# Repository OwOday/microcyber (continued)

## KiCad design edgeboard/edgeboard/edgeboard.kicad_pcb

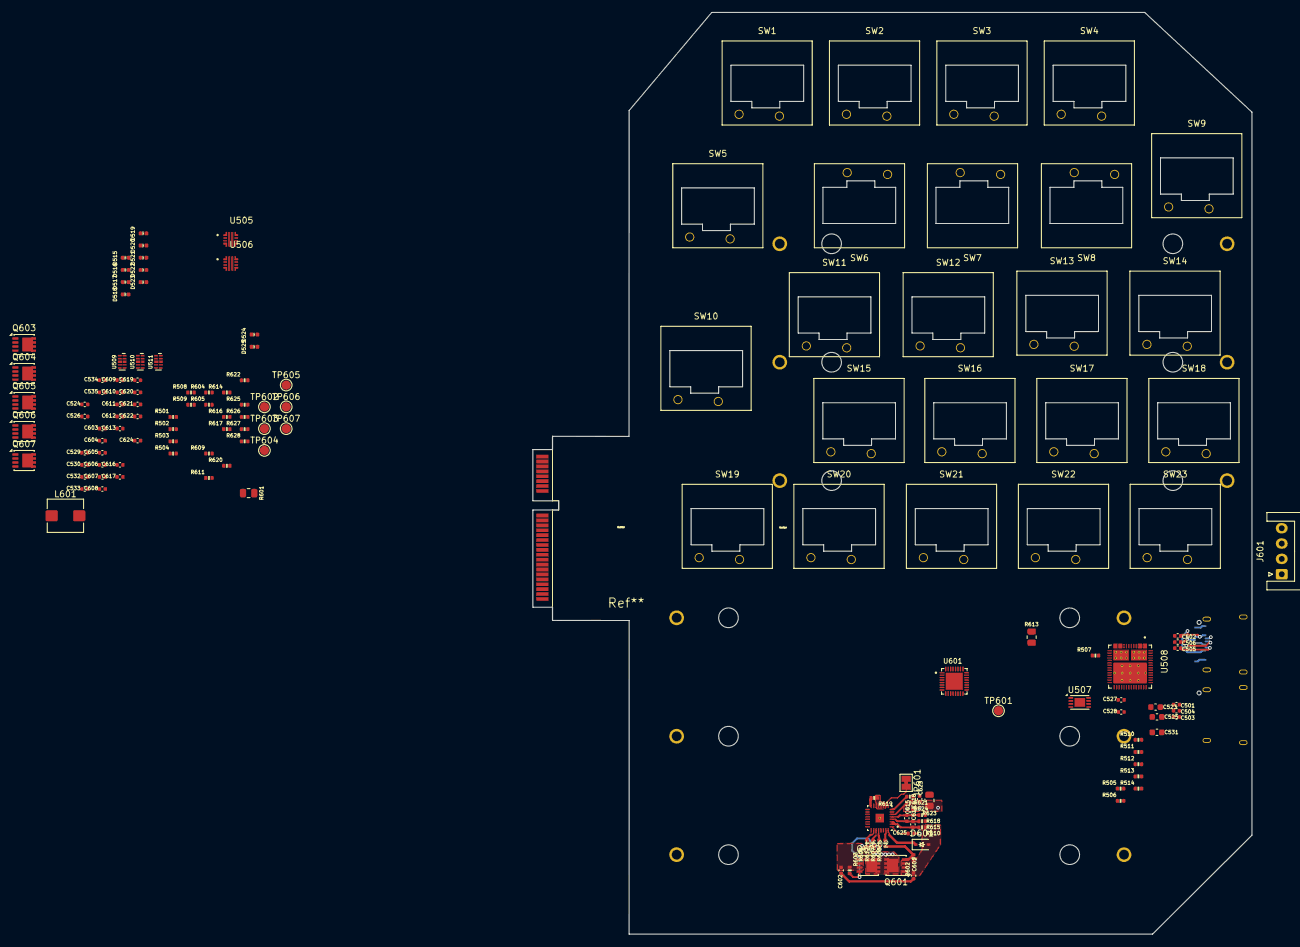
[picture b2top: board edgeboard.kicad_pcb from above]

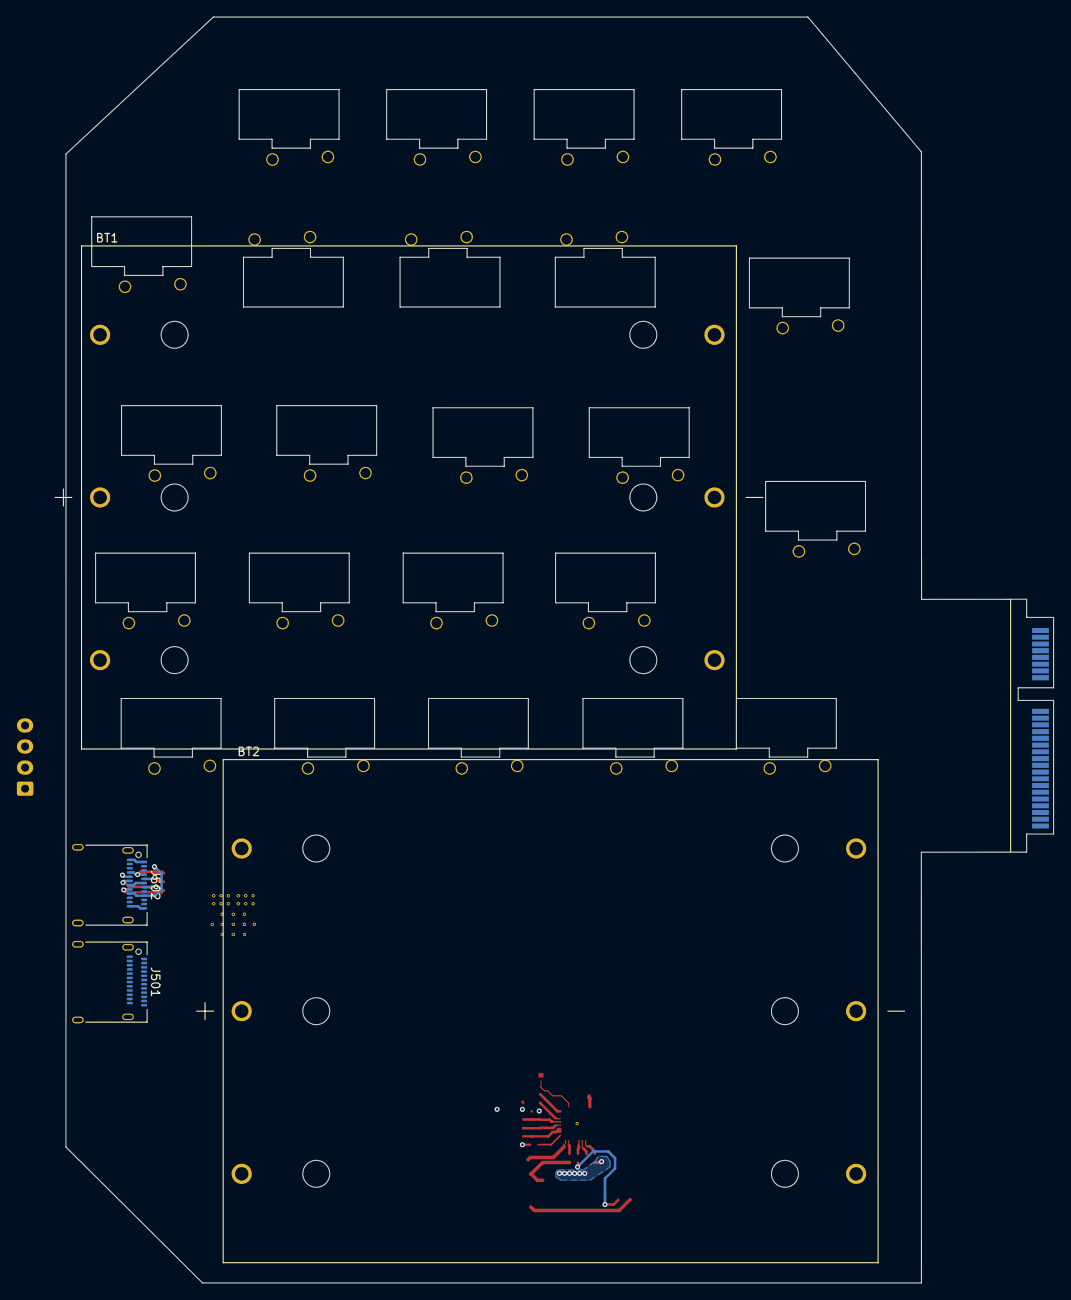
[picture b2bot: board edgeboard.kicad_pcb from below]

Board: 2 copper layers, 117.2 x 150.2 mm, 152 parts (4 on the bottom side), 101 nets.

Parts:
BT1, BT2: BK-18650-PC6; BAT_BK-18650-PC6
C501, C502, C524, C526, C527, C532, C533: 100nF/50V; C_0402_1005Metric
C503, C504, C505, C506: 47pF; C_0402_1005Metric
C523: 22uF/10V; C_0603_1608Metric
C525, C531: 10uF/10V; C_0603_1608Metric
C528: 4.7uF/10V; C_0402_1005Metric
C529, C530, C534, C535: 47pF/50V; C_0402_1005Metric
C601, C602, C613, C614, C615, C618, C623: 0.1u; C_0402_1005Metric
C603: 3x10uF MLCC; C_0402_1005Metric
C604, C605: 47n; C_0402_1005Metric
C606, C607, C608, C609: 10uF MLCC; C_0402_1005Metric
C610, C611: 33n; C_0402_1005Metric
C612: 0.47u; C_0402_1005Metric
C616: 33p; C_0402_1005Metric
C617: 1800p; C_0402_1005Metric
C619: 1u; C_0402_1005Metric
C620, C625: 2.2u; C_0402_1005Metric
C621: 15p; C_0402_1005Metric
C622: 680p; C_0402_1005Metric
C624: 100p; C_0402_1005Metric
D515, D516, D517, D518, D519, D520, D521, D522, D523, D524, D525: ESD9B3.3ST5GOSCT-ND; D_0402_1005Metric
D601: BAT54HT1; D_SOD-323
J501, J502: USB_C_Receptacle; USB_C_Receptacle_Amphenol_12401610E4-2A
J601: JST XH 4 pin; JST_XH_S4B-XH-A_1x04_P2.50mm_Horizontal
JP601: Jumper_2_Bridged; SolderJumper-2_P1.3mm_Bridged_Pad1.0x1.5mm
L601: 2.2uH 4.5A+; L_Bourns_SRP5030T
Q601, Q602, Q603, Q604, Q605, Q606: CSD17551Q3A; Vishay_PowerPAK_1212-8_Single
Q607: CSD25402Q3A; Vishay_PowerPAK_1212-8_Single
R501, R502, R503, R504, R508, R509, R510, R511, R512: 100K/1%; R_0402_1005Metric
R505, R506: 10K/1%; R_0402_1005Metric
R507: 100K; R_0402_1005Metric
R513, R612, R619: 10K; R_0402_1005Metric
R514: 19.1K/1%; R_0402_1005Metric
R601, R613: 10m; R_0805_2012Metric
R602, R603: 10M; R_0402_1005Metric
R604, R605: 4.99; R_0402_1005Metric
R606, R607: 5.1k; R_0402_1005Metric
R608, R610, R615, R618, R621, R624: 100; R_0402_1005Metric
R609: 1; R_0402_1005Metric
R611, R614, R617: 10; R_0402_1005Metric
R616: 40.2k; R_0402_1005Metric
R620: 10k; R_0402_1005Metric
R622, R625, R626, R628: TBD; R_0402_1005Metric
R623: 0.001; R_0805_2012Metric
R627: 137K; R_0402_1005Metric
Ref**: Val**; mpcie-full-card
SW1, SW2, SW3, SW4: SW_Push; SW_Kailh_Choc_Mini_1.25u_90deg
SW5: SW_Push; SW_Kailh_Choc_Mini_1.50u
SW6, SW7, SW8, SW11, SW12, SW13, SW14, SW15, SW16, SW17, SW18, SW19, SW20, SW21, SW22, SW23: SW_Push; SW_Kailh_Choc_Mini_1.00u
SW9: SW_Push; SW_Kailh_Choc_Mini_1.50u_90deg
SW10: SW_Push; SW_Kailh_Choc_Mini_ISOEnter_180deg
TP601: VBAT; TestPoint_Pad_D1.5mm
TP602: VCHARGE; TestPoint_Pad_D1.5mm
TP603: VSYSTEM; TestPoint_Pad_D1.5mm
TP604: PSYS; TestPoint_Pad_D1.5mm
TP605: PROCHOT; TestPoint_Pad_D1.5mm
TP606: IBAT; TestPoint_Pad_D1.5mm
TP607: CHRG_OK; TestPoint_Pad_D1.5mm
U505, U506: LM73100RPWR; IC_LM73100RPWR
U507: AT25DN512C-MAHF-T; DFN-8-1EP_3x2mm_P0.5mm_EP1.75x1.45mm
U508: TPS65988DHRSHR; IC_TPS65987DDHRSHR
U509, U510, U511: ULC0524P; Diodes_UDFN-10_1.0x2.5mm_P0.5mm
U601: BQ25710RSNT; QFN40P400X400X80-33N
U602: BQ40Z50RSMR-R2; QFN40P400X400X100-33N

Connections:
+3V3: C531.2, U508.5 (VIN_3V3)
+3V3_TPS: C525.2, C527.2, R505.2, R506.2, R512.1, U507.8 (VCC), U508.9 (LDO_3V3)
+5V: C528.2, U508.25 (PP1_CABLE), U508.46 (PP2_CABLE)
+12v: Ref**.38, Ref**.39, Ref**.40, Ref**.41, Ref**.42, Ref**.43, Ref**.44, Ref**.45, Ref**.46, Ref**.47, Ref**.48, Ref**.49, Ref**.50, Ref**.51, Ref**.52
/-BATT: C623.1, J601.4, R621.1, R623.1
/DISP1_HPD: R510.1, U508.30 (GPIO3(HPD1))
/DISP2_HPD: R511.1, U508.31 (GPIO4(HPD2))
/EXT_VBUS_SOURCE1: R501.2, U506.1 (EN/UVLO), U508.48 (GPIO16(PP_EXT1))
/EXT_VBUS_SOURCE2: R502.2, U505.1 (EN/UVLO), U508.49 (GPIO17(PP_EXT2))
/GPIO_1: D517.2 (A2), U511.1, U511.10 (NC)
/GPIO_2: D516.2 (A2), U511.4, U511.7 (NC)
/GPIO_3: D515.2 (A2), U511.2, U511.9 (NC)
/GPIO_4: D518.2 (A2), U511.5, U511.6 (NC)
/GPIO_5: D519.2 (A2), U510.1, U510.10 (NC)
/GPIO_6: D520.2 (A2), U510.4, U510.7 (NC)
/GPIO_7: D521.2 (A2), U510.2, U510.9 (NC)
/GPIO_8: D522.2 (A2), U510.5, U510.6 (NC)
/PACK+: C601.1, D601.2 (A), J601.1, Q601.1 (S), Q601.2 (S), Q601.3 (S), R602.1, R610.1
/SMB_ALERT: D525.2 (A2), U509.4, U509.7 (NC)
/SMB_CLK: D524.2 (A2), U509.2, U509.9 (NC), U601.13 (SCL), U602.19 (SMBC)
/SMB_DATA: D523.2 (A2), U509.1, U509.10 (NC), U601.12 (SDA), U602.18 (SMBD)
/USBC1_CC1: C504.1, J501.A5 (CC1), U508.24 (C1_CC1)
/USBC1_CC2: C503.1, J501.B5 (CC2), U508.26 (C1_CC2)
/USBC1_SBU1: C524.2, C529.1, J501.A8 (SBU1), R504.2
/USBC1_SBU2: C526.2, C530.1, J501.B8 (SBU2), R503.2
/USBC1_USB2_D+: J501.A6 (D+), J501.B6 (D+)
/USBC1_USB2_D-: J501.A7 (D-), J501.B7 (D-)
/USBC1_VBUS: C501.1, J501.A4 (VBUS), J501.A9 (VBUS), J501.B4 (VBUS), J501.B9 (VBUS), U506.6 (OUT), U508.13 (VBUS1)
/USBC2_CC1: C506.1, J502.A5 (CC1), U508.45 (C2_CC1)
/USBC2_CC2: C505.1, J502.B5 (CC2), U508.47 (C2_CC2)
/USBC2_SBU1: C532.2, C534.1, J502.A8 (SBU1), R509.2
/USBC2_SBU2: C533.2, C535.1, J502.B8 (SBU2), R508.2
/USBC2_USB2_D+: J502.A6 (D+), J502.B6 (D+)
/USBC2_USB2_D-: J502.A7 (D-), J502.B7 (D-)
/USBC2_VBUS: C502.1, J502.A4 (VBUS), J502.A9 (VBUS), J502.B4 (VBUS), J502.B9 (VBUS), U505.6 (OUT), U508.3 (VBUS2)
/VBAT: C602.2, C613.2, Q602.1 (S), Q602.2 (S), Q602.3 (S), R603.1, R612.1, R613.1, R614.1, TP601.1 (1_1)
/VBATSNS: C613.1, Q607.1 (D), Q607.2 (D), Q607.3 (D), R611.1, R613.2
/VBUS_5VIN: U505.5 (IN), U506.5 (IN)
/VCHARGE: C603.1, R601.1, R604.1, R609.1, TP602.1 (1_1), U508.1 (PP_HV2), U508.11 (PP_HV1)
/VSYSTEM: C606.1, C607.1, C608.1, C609.1, Q604.5 (D), Q607.5 (S), TP603.1 (1_1), U601.22 (VSYS)
GND: C501.2, C502.2, C503.2, C504.2, C505.2, C506.2, C523.1, C525.1, C527.1, C528.1, C529.2, C530.2, C531.1, C534.2, C535.2, C603.2, C606.2, C607.2, C608.2, C609.2, C610.2, C611.2, C612.2, C616.2, C617.2, C618.1, C619.2, C620.2, C621.2, C622.2, C623.2, C624.2, C625.2, D515.1 (A1), D516.1 (A1), D517.1 (A1), D518.1 (A1), D519.1 (A1), D520.1 (A1), D521.1 (A1), D522.1 (A1), D523.1 (A1), D524.1 (A1), D525.1 (A1), J501.A1 (GND), J501.A12 (GND), J501.B1 (GND), J501.B12 (GND), J502.A1 (GND), J502.A12 (GND), J502.B1 (GND), J502.B12 (GND), JP601.1 (A), Q605.1 (S), Q605.2 (S), Q605.3 (S), Q606.1 (S), Q606.2 (S), Q606.3 (S), R501.1, R502.1, R507.1, R510.2, R511.2, R513.1, R514.2, R619.1, R623.2, R624.1, R625.2, R627.2, R628.2, Ref**.17, Ref**.18, Ref**.19, Ref**.20, Ref**.21, Ref**.22, Ref**.23, Ref**.24, Ref**.25, Ref**.26, Ref**.27, Ref**.29, U505.2 (OVLO), U505.4 (PGTH), U505.8 (GND), U505.9 (IMON), U506.2 (OVLO), U506.4 (PGTH), U506.8 (GND), U506.9 (IMON), U507.4 (GND), U507.9 (GND), U508.10 (ADCIN2), U508.20 (GND), U508.51 (GND__1), U508.59 (THERMALPAD(PPAD)), U508.59_1 (THERMALPAD(PPAD)), U508.59_2 (THERMALPAD(PPAD)), U508.59_3 (THERMALPAD(PPAD)), U508.59_4 (THERMALPAD(PPAD)), U508.59_5 (THERMALPAD(PPAD)), U508.59_6 (THERMALPAD(PPAD)), U508.59_7 (THERMALPAD(PPAD)), U508.59_8 (THERMALPAD(PPAD)), U508.59_9 (THERMALPAD(PPAD)), U508.59_10 (THERMALPAD(PPAD)), U508.59_11 (THERMALPAD(PPAD)), U509.3 (VSS), U509.8 (VSS), U510.3 (VSS), U510.8 (VSS), U511.3 (VSS), U511.8 (VSS), U601.5 (OTG/VAP), U601.14 (CMPIN), U601.27 (PGND), U602.9 (VSS), U602.11 (TS2), U602.12 (TS3), U602.13 (TS4), U602.17 (~DISP), U602.23 (PTC), U602.24 (PTCEN), U602.33 (EXP), U602.33_1 (EXP__1)
unnamed: C601.2, C602.1
unnamed: C617.1, R616.2
unnamed: C622.1, R620.2
unnamed: D601.1 (K), U602.32 (BAT)
unnamed: J601.2, R615.1
unnamed: J601.3, R618.1
unnamed: JP601.2 (B), U602.10 (TS1)
unnamed: Q601.5 (D), Q602.5 (D), R608.1
unnamed: Q601.4 (G), R602.2, R606.1
unnamed: Q602.4 (G), R603.2, R607.1
unnamed: Q603.5 (D), R601.2, R605.1
unnamed: Q603.4 (G), U601.31 (HIDRV1)
unnamed: Q604.4 (G), U601.24 (HIDRV2)
unnamed: C604.1, L601.1, Q603.1 (S), Q603.2 (S), Q603.3 (S), Q605.5 (D), U601.32 (SW1)
unnamed: Q605.4 (G), U601.29 (LODRV1)
unnamed: C605.1, L601.2, Q604.1 (S), Q604.2 (S), Q604.3 (S), Q606.5 (D), U601.23 (SW2)
unnamed: Q606.4 (G), U601.26 (LODRV2)
unnamed: Q607.4 (G), U601.21 (~BATDRV)
unnamed: U507.2 (MISO), U508.36 (SPI_POCI)
unnamed: U507.5 (MOSI), U508.37 (SPI_PICO)
unnamed: U507.6 (SCK), U508.38 (SPI_CLK)
unnamed: U507.1 (~CS), U508.39 (~SPI_CS)
unnamed: R512.2, R514.1, U508.6 (ADCIN1)
unnamed: U508.8 (DRAIN1), U508.15 (DRAIN1__1), U508.19 (DRAIN1__2), U508.58 (DRAIN1__3), U508.58_1 (DRAIN1_PAD), U508.58_2 (DRAIN1_PAD), U508.58_3 (DRAIN1_PAD), U508.58_4 (DRAIN1_PAD), U508.58_5 (DRAIN1_PAD), U508.58_6 (DRAIN1_PAD)
unnamed: U508.7 (DRAIN2), U508.52 (DRAIN2__1), U508.56 (DRAIN2__2), U508.57 (DRAIN2__3), U508.57_1 (DRAIN2_PAD), U508.57_2 (DRAIN2_PAD), U508.57_3 (DRAIN2_PAD), U508.57_4 (DRAIN2_PAD), U508.57_5 (DRAIN2_PAD), U508.57_6 (DRAIN2_PAD)
unnamed: R507.2, U508.17 (GPIO1)
unnamed: R513.2, U508.44 (HRESET)
unnamed: R505.1, U508.27 (I2C1_SCL)
unnamed: R506.1, U508.28 (I2C1_SDA)
unnamed: C523.2, U508.35 (LDO_1V8)
unnamed: U509.5, U509.6 (NC)
unnamed: C611.1, R605.2, U601.2 (ACN)
unnamed: C610.1, R604.2, U601.3 (ACP)
unnamed: C604.2, U601.30 (BTST1)
unnamed: C605.2, U601.25 (BTST2)
unnamed: R622.2, R625.1, U601.18 (CELL_BATPRESZ)
unnamed: TP607.1 (1_1), U601.4 (CHRG_OK)
unnamed: C616.1, R616.1, U601.16 (COMP1)
unnamed: C621.1, R620.1, U601.17 (COMP2)
unnamed: C624.1, R627.1, U601.8 (IADPT)
unnamed: TP606.1 (1_1), U601.9 (IBAT)
unnamed: R626.2, R628.1, U601.6 (ILIM_HIZ)
unnamed: TP604.1 (1_1), U601.10 (PSYS)
unnamed: C620.1, R617.2, U601.28 (REGN)
unnamed: R614.2, U601.19 (SRN)
unnamed: R611.2, U601.20 (SRP)
unnamed: C612.1, R609.2, U601.1 (VBUS)
unnamed: C619.1, R617.1, R622.1, R626.1, U601.7 (VDDA)
unnamed: TP605.1 (1_1), U601.11 (~PROCHOT)
unnamed: R606.2, U602.31 (CHG)
unnamed: R607.2, U602.28 (DSG)
unnamed: R612.2, U602.27 (PACK)
unnamed: C625.1, U602.1 (PBI)
unnamed: R624.2, U602.6 (SRN)
unnamed: R621.2, U602.8 (SRP)
unnamed: C615.1, C618.2, R618.2, U602.5 (VC1)
unnamed: C614.1, C615.2, R615.2, U602.4 (VC2)
unnamed: C614.2, R610.2, U602.2 (VC4), U602.3 (VC3)
unnamed: R608.2, U602.26 (VCC)
unnamed: R619.2, U602.16 (~PRES/~SHUTDN)

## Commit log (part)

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2026-03-20 initial
2026-03-21 more work on custom usb-c power
2026-03-26 finished schematic draft and started placing components
2026-03-28 commit before removing duplicated glasgow
2026-03-29 is this a differential pair?
2026-03-29 differential pairs fixed?
2026-03-30 before board exclusion
2026-03-30 REV 0
2026-04-06 went back to the drawing board
2026-04-07 some power stuff (unfinished)
2026-04-07 power finished started diff pairs
2026-04-07 rpi edgeboard
2026-04-07 fixed 5v->3v bug
2026-04-08 hdmi-power-finished?
2026-04-08 all power, diff pairs done, all components placed (final spot?) just some small wires left to route
2026-04-08 fill ground planes
2026-04-19 V4 done ???
2026-04-19 hdmi diff pair remains??
2026-04-19 some schem fixes
2026-04-20 more fixes, tweaks, pretty
2026-04-21 small fix
2026-04-22 small fix 2
2026-04-25 added USB-C
2026-04-25 switch xt60 to terminal block
2026-04-25 move glasgow zohm
2026-04-25 enable sml
2026-04-25 add fids to back
2026-04-26 move the power around just for fun
2026-04-26 chamfer that shit
2026-04-26 fix layer names
2026-04-26 silk screen fix
2026-04-26 silk screen fix 2
2026-04-26 remove wrong comments
2026-04-26 round edges
2026-04-26 zone
2026-04-26 edges
2026-05-01 last push before editing with the grid view (gonna break everything)
2026-05-01 fix a trace. then do the weird shit
2026-05-02 added MPN to all parts by hand :'(
2026-05-03 Prototype
2026-05-14 change adc to 0 ohm
2026-05-14 add points to program eeprom
2026-06-09 resend fab
